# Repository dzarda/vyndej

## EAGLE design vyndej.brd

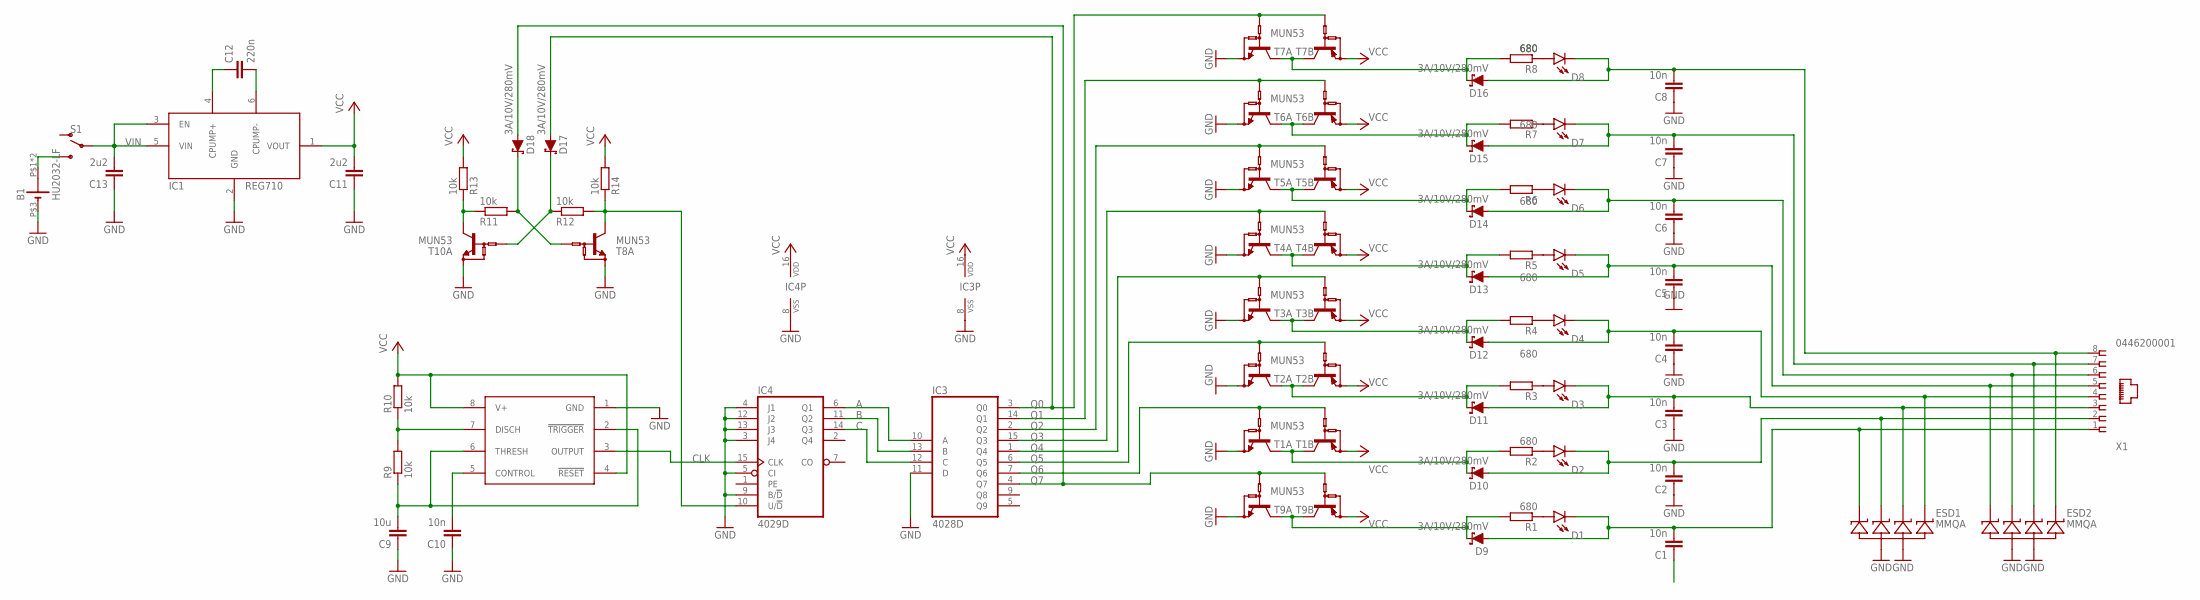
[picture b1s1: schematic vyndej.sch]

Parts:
B1: HU2032-LF
C1, C2, C3, C4, C5, C6, C7, C8, C10: 10n; C0603
C9: 10u; C1210K
C11, C13: 2u2; C0603
C12: 220n; C0603
D1, D2, D3, D4, D5, D6, D7, D8: RED; PLCC-2
D9, D10, D11, D12, D13, D14, D15, D16, D17, D18: 3A/10V/280mV; SOD-323
ESD1, ESD2: MMQA; SC-74
IC1: REG710; SOT23-6
IC2: LMC555; SO08
IC3: 4028D; SO16
IC4: 4029D; SO16
R1, R2, R3, R4, R5, R6, R7, R8: 680; R0603
R9, R10, R11, R12, R13, R14: 10k; R0603
S1: SWITCH-SPDT-SMD-RIGHT-ANGLE; SWITCH_SPST_SMD_A
T1, T2, T3, T4, T5, T6, T7, T8, T9, T10: MUN53; SOT-363
X1: 0446200001

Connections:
A: IC3.10 (A), IC4.6 (Q1)
B: IC3.13 (B), IC4.11 (Q2)
C: IC3.12 (C), IC4.14 (Q3)
CLK: IC2.3 (OUTPUT), IC4.15 (CLK)
GND: B1.P$3 (-), C2.1, C3.1, C4.1, C5.1, C6.1, C7.1, C8.1, C9.1, C10.1, C11.1, C13.1, ESD1.2 (A1), ESD1.5 (A2), ESD2.2 (A1), ESD2.5 (A2), IC1.2 (GND), IC2.1 (GND), IC3.8 (VSS), IC3.11 (D), IC4.3 (J4), IC4.4 (J1), IC4.5 (CI), IC4.8 (VSS), IC4.9 (B/!D), IC4.12 (J2), IC4.13 (J3), T1.P$1 (E), T2.P$1 (E), T3.P$1 (E), T4.P$1 (E), T5.P$1 (E), T6.P$1 (E), T7.P$1 (E), T8.P$1 (E), T9.P$1 (E), T10.P$1 (E)
unnamed: D8.A, R8.1
unnamed: D7.A, R7.1
unnamed: D6.A, R6.1
unnamed: D5.A, R5.1
unnamed: D1.A, R1.1
unnamed: D2.A, R2.1
unnamed: D3.A, R3.1
unnamed: D4.A, R4.1
unnamed: C1.2, D1.C, D9.A, ESD1.1 (C), X1.1
unnamed: C2.2, D2.C, D10.A, ESD1.3 (C1), X1.2
unnamed: C3.2, D3.C, D11.A, ESD1.4 (C2), X1.3
unnamed: C4.2, D4.C, D12.A, ESD1.6 (C3), X1.4
unnamed: C5.2, D5.C, D13.A, ESD2.1 (C), X1.5
unnamed: C6.2, D6.C, D14.A, ESD2.3 (C1), X1.6
unnamed: C7.2, D7.C, D15.A, ESD2.4 (C2), X1.7
unnamed: D16.C, R8.2, T7.P$3 (C), T7.P$6 (C)
unnamed: D18.C, R11.2, T8.P$2 (B)
unnamed: D15.C, R7.2, T6.P$3 (C), T6.P$6 (C)
unnamed: C8.2, D8.C, D16.A, ESD2.6 (C3), X1.8
unnamed: D17.C, R12.1, T10.P$2 (B)
unnamed: IC4.10 (U/!D), R12.2, R14.1, T8.P$6 (C)
unnamed: R11.1, R13.1, T10.P$6 (C)
unnamed: D12.C, R4.2, T3.P$3 (C), T3.P$6 (C)
unnamed: C12.1, IC1.4 (CPUMP+)
unnamed: C12.2, IC1.6 (CPUMP-)
unnamed: C10.2, IC2.5 (CONTROL)
unnamed: C9.2, IC2.2 (!TRIGGER), IC2.6 (THRESH), R9.1
unnamed: IC2.7 (DISCH), R9.2, R10.1
unnamed: B1.P$1 (+), B1.P$2 (+), S1.3 (S)
unnamed: D14.C, R6.2, T5.P$3 (C), T5.P$6 (C)
unnamed: D13.C, R5.2, T4.P$3 (C), T4.P$6 (C)
unnamed: D9.C, R1.2, T9.P$3 (C), T9.P$6 (C)
unnamed: D10.C, R2.2, T1.P$3 (C), T1.P$6 (C)
unnamed: D11.C, R3.2, T2.P$3 (C), T2.P$6 (C)
Q0: D17.A, IC3.3 (Q0), T7.P$2 (B), T7.P$5 (B)
Q1: IC3.14 (Q1), T6.P$2 (B), T6.P$5 (B)
Q2: IC3.2 (Q2), T5.P$2 (B), T5.P$5 (B)
Q3: IC3.15 (Q3), T4.P$2 (B), T4.P$5 (B)
Q4: IC3.1 (Q4), T3.P$2 (B), T3.P$5 (B)
Q5: IC3.6 (Q5), T2.P$2 (B), T2.P$5 (B)
Q6: IC3.7 (Q6), T1.P$2 (B), T1.P$5 (B)
Q7: D18.A, IC3.4 (Q7), T9.P$2 (B), T9.P$5 (B)
VCC: C11.2, IC1.1 (VOUT), IC2.4 (!RESET), IC2.8 (V+), IC3.16 (VDD), IC4.16 (VDD), R10.2, R13.2, R14.2, T1.P$4 (E), T2.P$4 (E), T3.P$4 (E), T4.P$4 (E), T5.P$4 (E), T6.P$4 (E), T7.P$4 (E), T9.P$4 (E)
VIN: C13.2, IC1.3 (EN), IC1.5 (VIN), S1.2

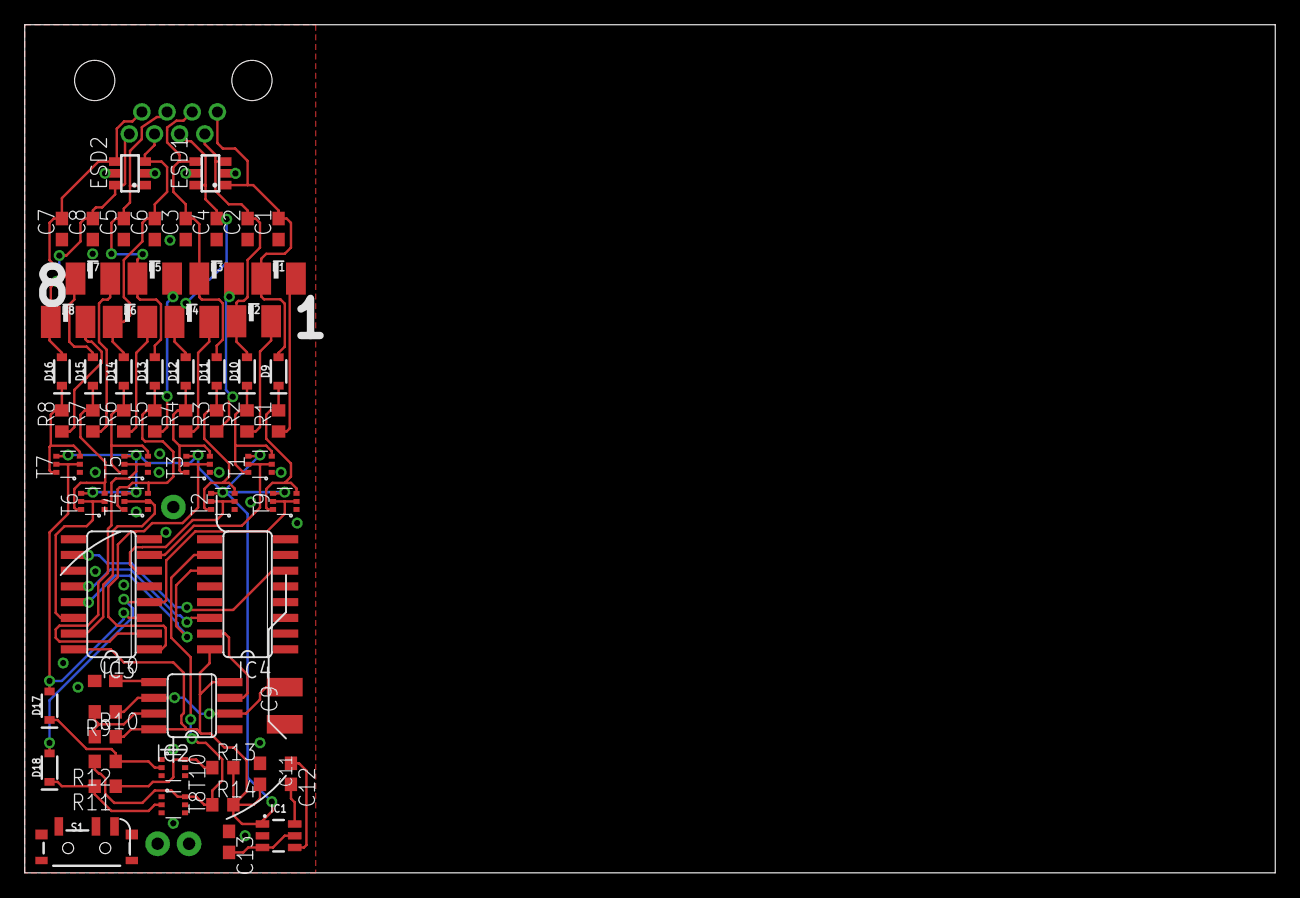
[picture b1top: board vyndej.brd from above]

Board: 2 copper layers, 101.0 x 68.5 mm, 64 parts (1 on the bottom side), 49 nets.

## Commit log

2020-01-07 Martin is king

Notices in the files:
parts and their libraries:
SparkFun-DiscreteSemi: Licensing: Creative Commons ShareAlike 4.0 International - https://creativecommons.org/licenses/by-sa/4.0
